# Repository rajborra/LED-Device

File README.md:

# LED-Device

A device that toggles through five states, activated with a button push:

1. Off
2. Full Brightness
3. Half Brightness
4. 1/4th Brightness
5. Flashing at 2 Hz

The MCU used was an ATMEGA328. The battery used had a supply voltage of 9V.

Note: the signal from the button to the MCU is missing; either fix the ECAD design or solder on a wire in the physical design as a workaround.

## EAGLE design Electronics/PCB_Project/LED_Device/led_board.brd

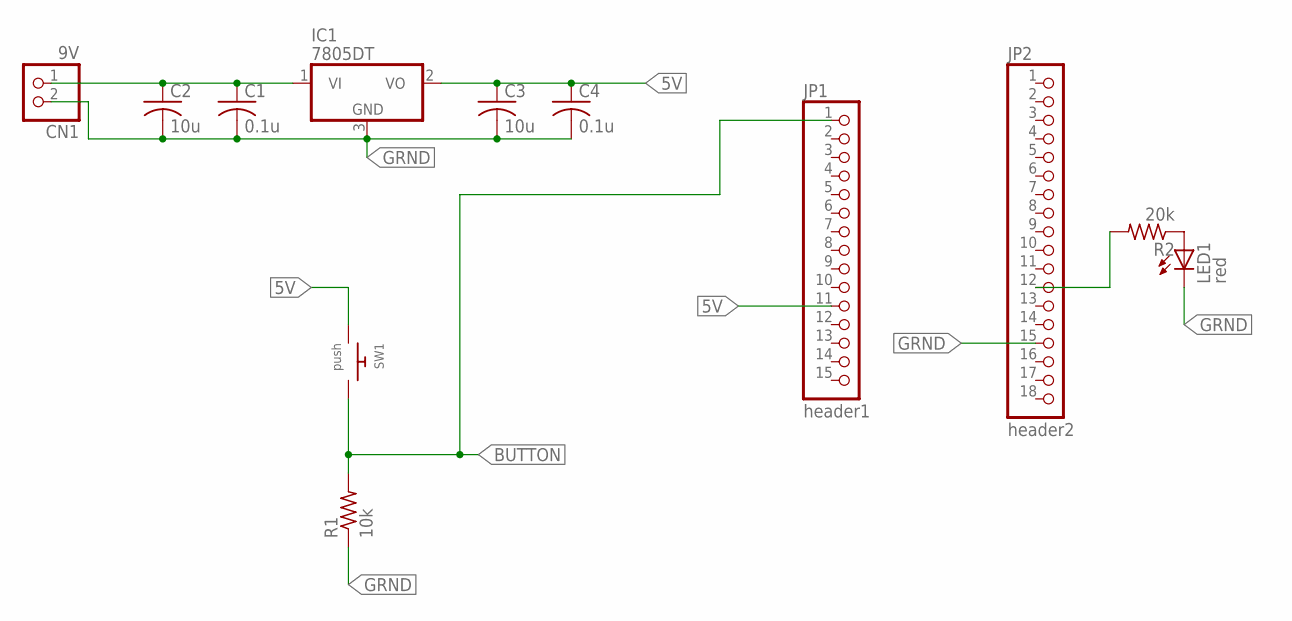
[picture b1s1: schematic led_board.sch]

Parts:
C1, C4: 0.1u; C0805
C2, C3: 10u; C0805
CN1: 9V; JST-PH-2-SMT
IC1: 7805DT; TO252
JP1: header1; 1X15
JP2: header2; 1X18
LED1: red; CHIPLED_0603
R1: 10k; M0805
R2: 20k; M0805
SW1: push; PUSHBUTTON_SMD_SJ

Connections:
5V: C3.1, C4.1, IC1.2 (VO), JP1.11, SW1.P$1
BUTTON: JP1.1, R1.2, SW1.P$2
GRND: C1.2, C2.2, C3.2, C4.2, CN1.2 (1), IC1.3 (GND), JP2.15, LED1.C, R1.1
unnamed: C1.1, C2.1, CN1.1 (2), IC1.1 (VI)
unnamed: LED1.A, R2.1
unnamed: JP2.12, R2.2

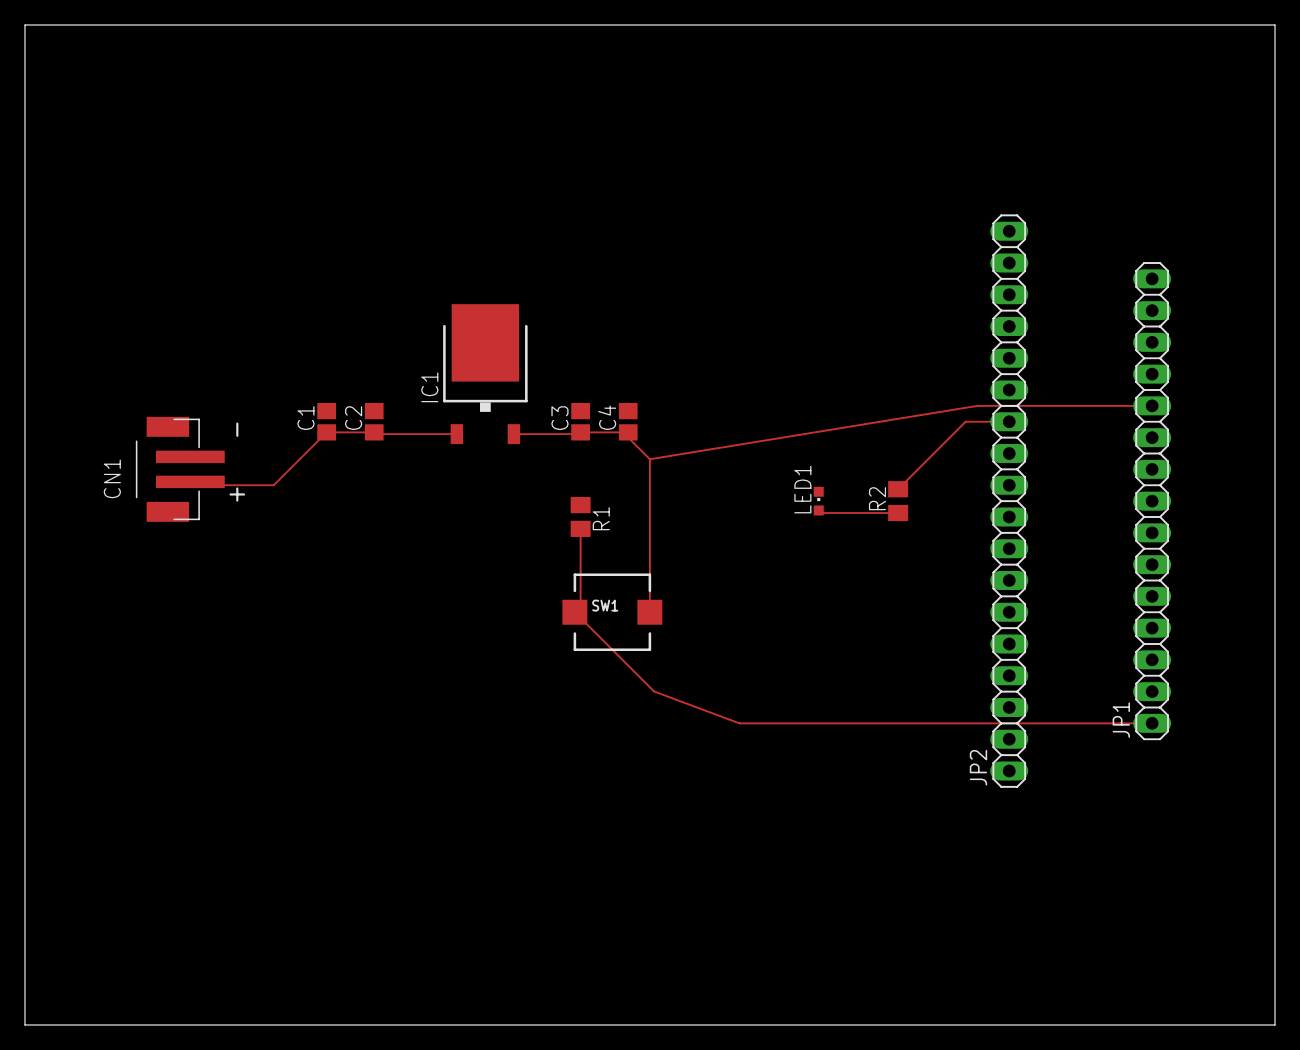
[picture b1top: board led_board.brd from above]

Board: 2 copper layers, 100.0 x 80.0 mm, 12 parts (0 on the bottom side), 6 nets.

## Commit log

2018-11-01 initial files
2018-11-08 first schematic and board design draft
2018-11-12 added working ground plane
2018-11-17 changed PCB design to have ATMEGA328 and crystal
2018-11-17 removed extra files
2018-11-19 first mechanical design draft
2018-11-24 finished draft of bottom piece
2018-11-27 created lid and edited bottom size
2018-12-06 final files
2018-12-06 tracked some updated files
